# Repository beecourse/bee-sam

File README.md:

bee-sam
=======

This [bee](https://github.com/beecourse) provides a **s**peaker **am**plifier.

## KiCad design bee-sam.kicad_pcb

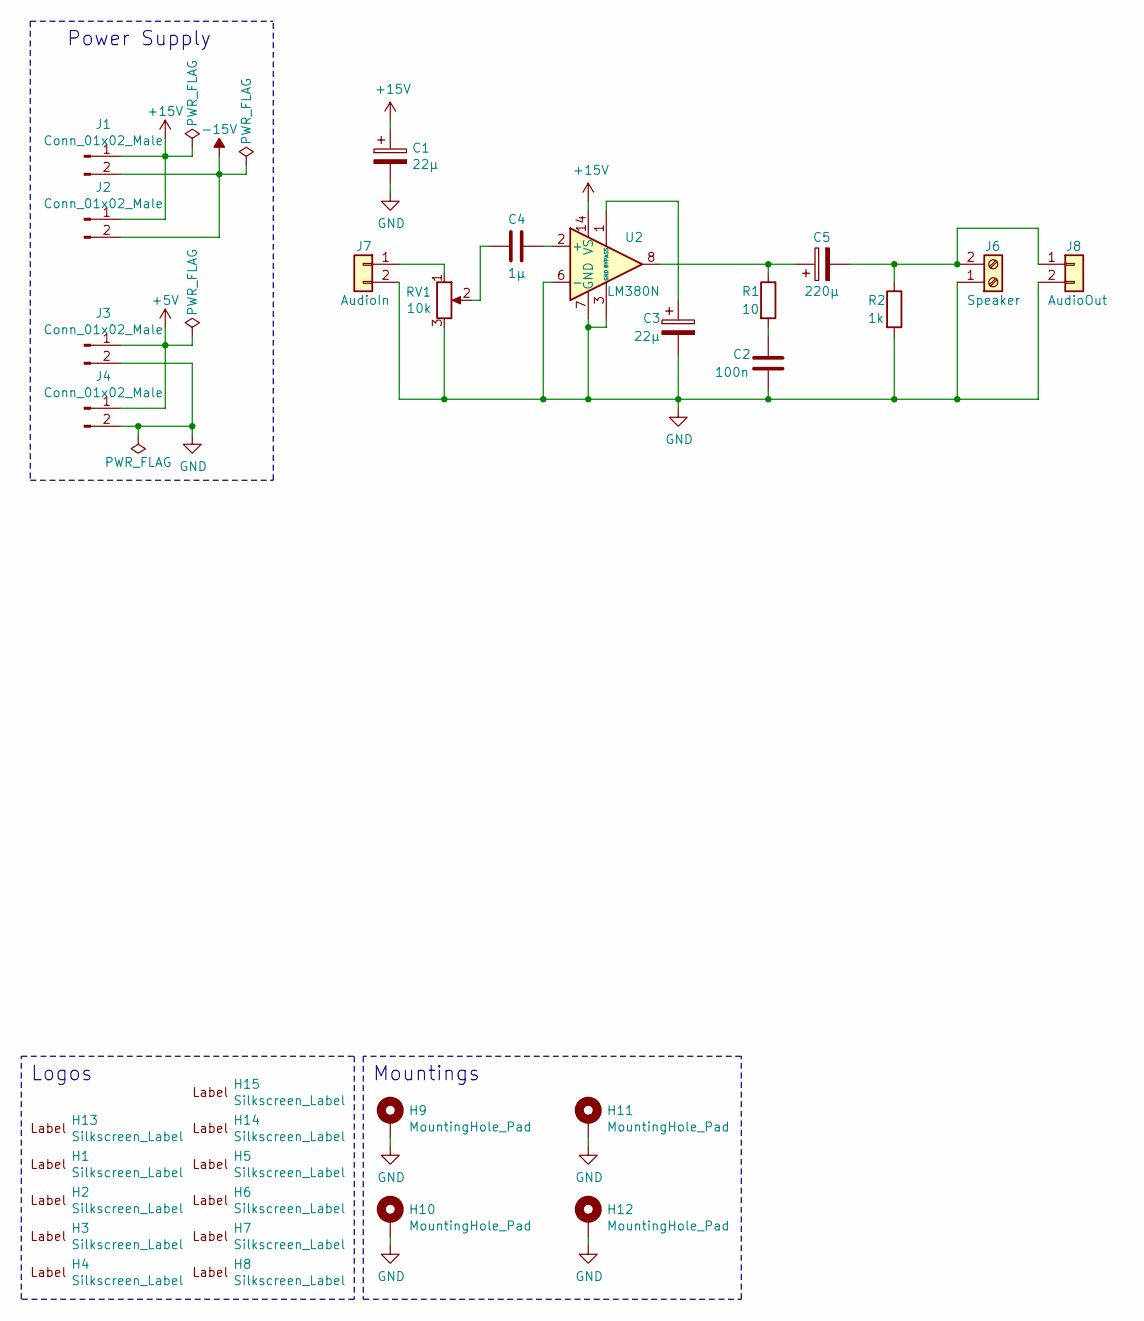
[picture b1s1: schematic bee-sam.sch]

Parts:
C1, C3: 22µ; CP_Radial_D8.0mm_P2.50mm_P3.80mm_P5.00mm
C2: 100n; C_Rect_L7.2mm_W3.0mm_P5.00mm_FKS2_FKP2_MKS2_MKP2
C4: 1µ; C_Rect_L7.2mm_W3.0mm_P5.00mm_FKS2_FKP2_MKS2_MKP2
C5: 220µ; CP_Radial_D8.0mm_P2.50mm_P3.80mm_P5.00mm
H1, H2: Silkscreen_Label; Text_U_B+_Silkscreen
H3, H4: Silkscreen_Label; Text_U_B-_Silkscreen
H5, H6: Silkscreen_Label; Text_U_B2_Silkscreen
H7, H8: Silkscreen_Label; Symbol_GND_Silkscreen
H9, H10, H11, H12: MountingHole_Pad; MountingHole_3.2mm_M3_ISO7380_Pad
H13: Silkscreen_Label; EMT-Logo_5.1x2.5mm_Silkscreen
H14: Silkscreen_Label; BEE-Logo_Silkscreen_small
H15: Silkscreen_Label; EMT-Logo_8.2x4.1mm_Silkscreen
J1, J2, J3, J4: Conn_01x02_Male; PinHeader_1x02_P2.54mm_Vertical
J6: Speaker; TerminalBlock_bornier-2_P5.08mm
J7: AudioIn; PinHeader_1x02_P2.54mm_Vertical
J8: AudioOut; PinHeader_1x02_P2.54mm_Vertical
R1: 10; R_Axial_DIN0207_L6.3mm_D2.5mm_P7.62mm_Horizontal
R2: 1k; R_Axial_DIN0207_L6.3mm_D2.5mm_P7.62mm_Horizontal
RV1: 10k; Potentiometer_Piher_PT-6-V_Vertical
U2: LM380N; DIP-14_W7.62mm

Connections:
+5V: J3.1, J4.1
+15V: C1.1, J1.1, J2.1, U2.14 (VS)
-15V: J1.2, J2.2
GND: C1.2, C2.2, C3.2, H9.1, H10.1, H11.1, H12.1, J3.2, J4.2, J6.1, J7.2, J8.2, R2.2, RV1.3, U2.3 (GND), U2.4 (GND), U2.5 (GND), U2.6 (-), U2.7 (GND), U2.10 (GND), U2.11 (GND), U2.12 (GND)
unnamed: C2.1, R1.2
unnamed: C3.1, U2.1 (BYPASS)
unnamed: C4.1, U2.2 (+)
unnamed: C4.2, RV1.2
unnamed: C5.1, R1.1, U2.8
unnamed: C5.2, J6.2, J8.1, R2.1
unnamed: J7.1, RV1.1

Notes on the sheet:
Power Supply
Logos
Mountings

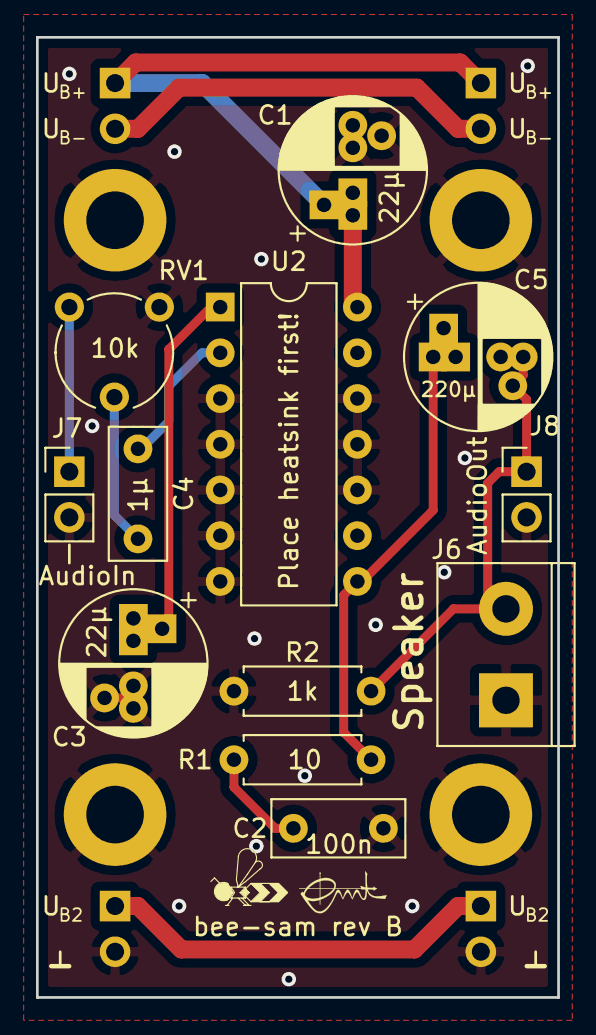
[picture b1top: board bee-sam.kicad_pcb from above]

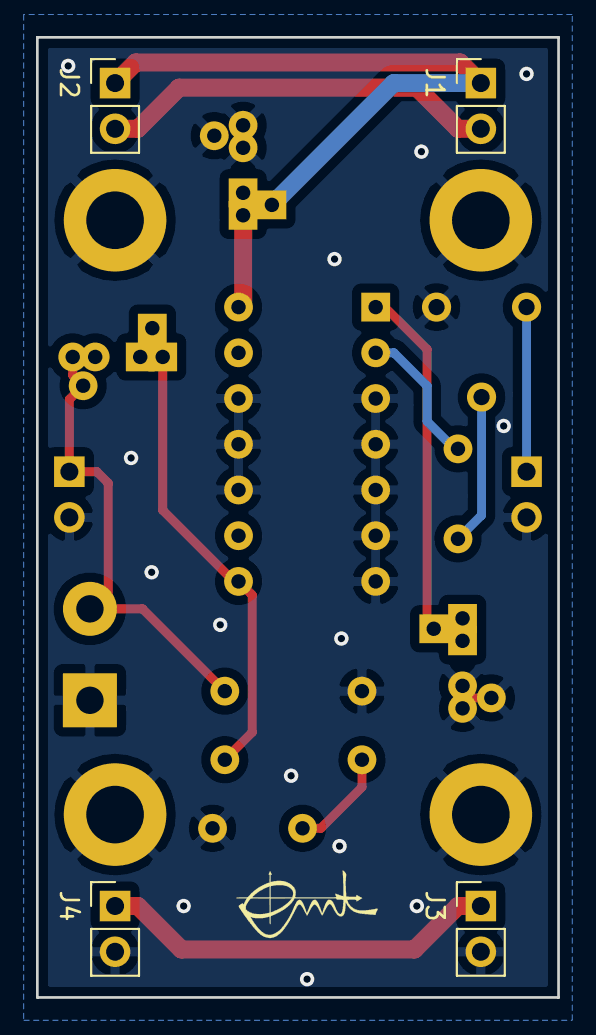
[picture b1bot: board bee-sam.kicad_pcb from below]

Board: 2 copper layers, 29.0 x 53.3 mm, 31 parts (5 on the bottom side), 11 nets.

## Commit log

2020-12-10 Add .gitignore
2020-12-10 Add license
2020-12-10 Add readme
2020-12-10 Add schematic and pcb
2021-12-13 gitignore: Add backup files ending on -bak
2021-12-13 Refactoring
    * Replace capacitor footprints with more versatile footprints
    * Print device values on pcb
    * Adapt spacings between components and heatsink
2023-03-17 Add figure showing top view of PCB
2023-03-17 Resize figure
